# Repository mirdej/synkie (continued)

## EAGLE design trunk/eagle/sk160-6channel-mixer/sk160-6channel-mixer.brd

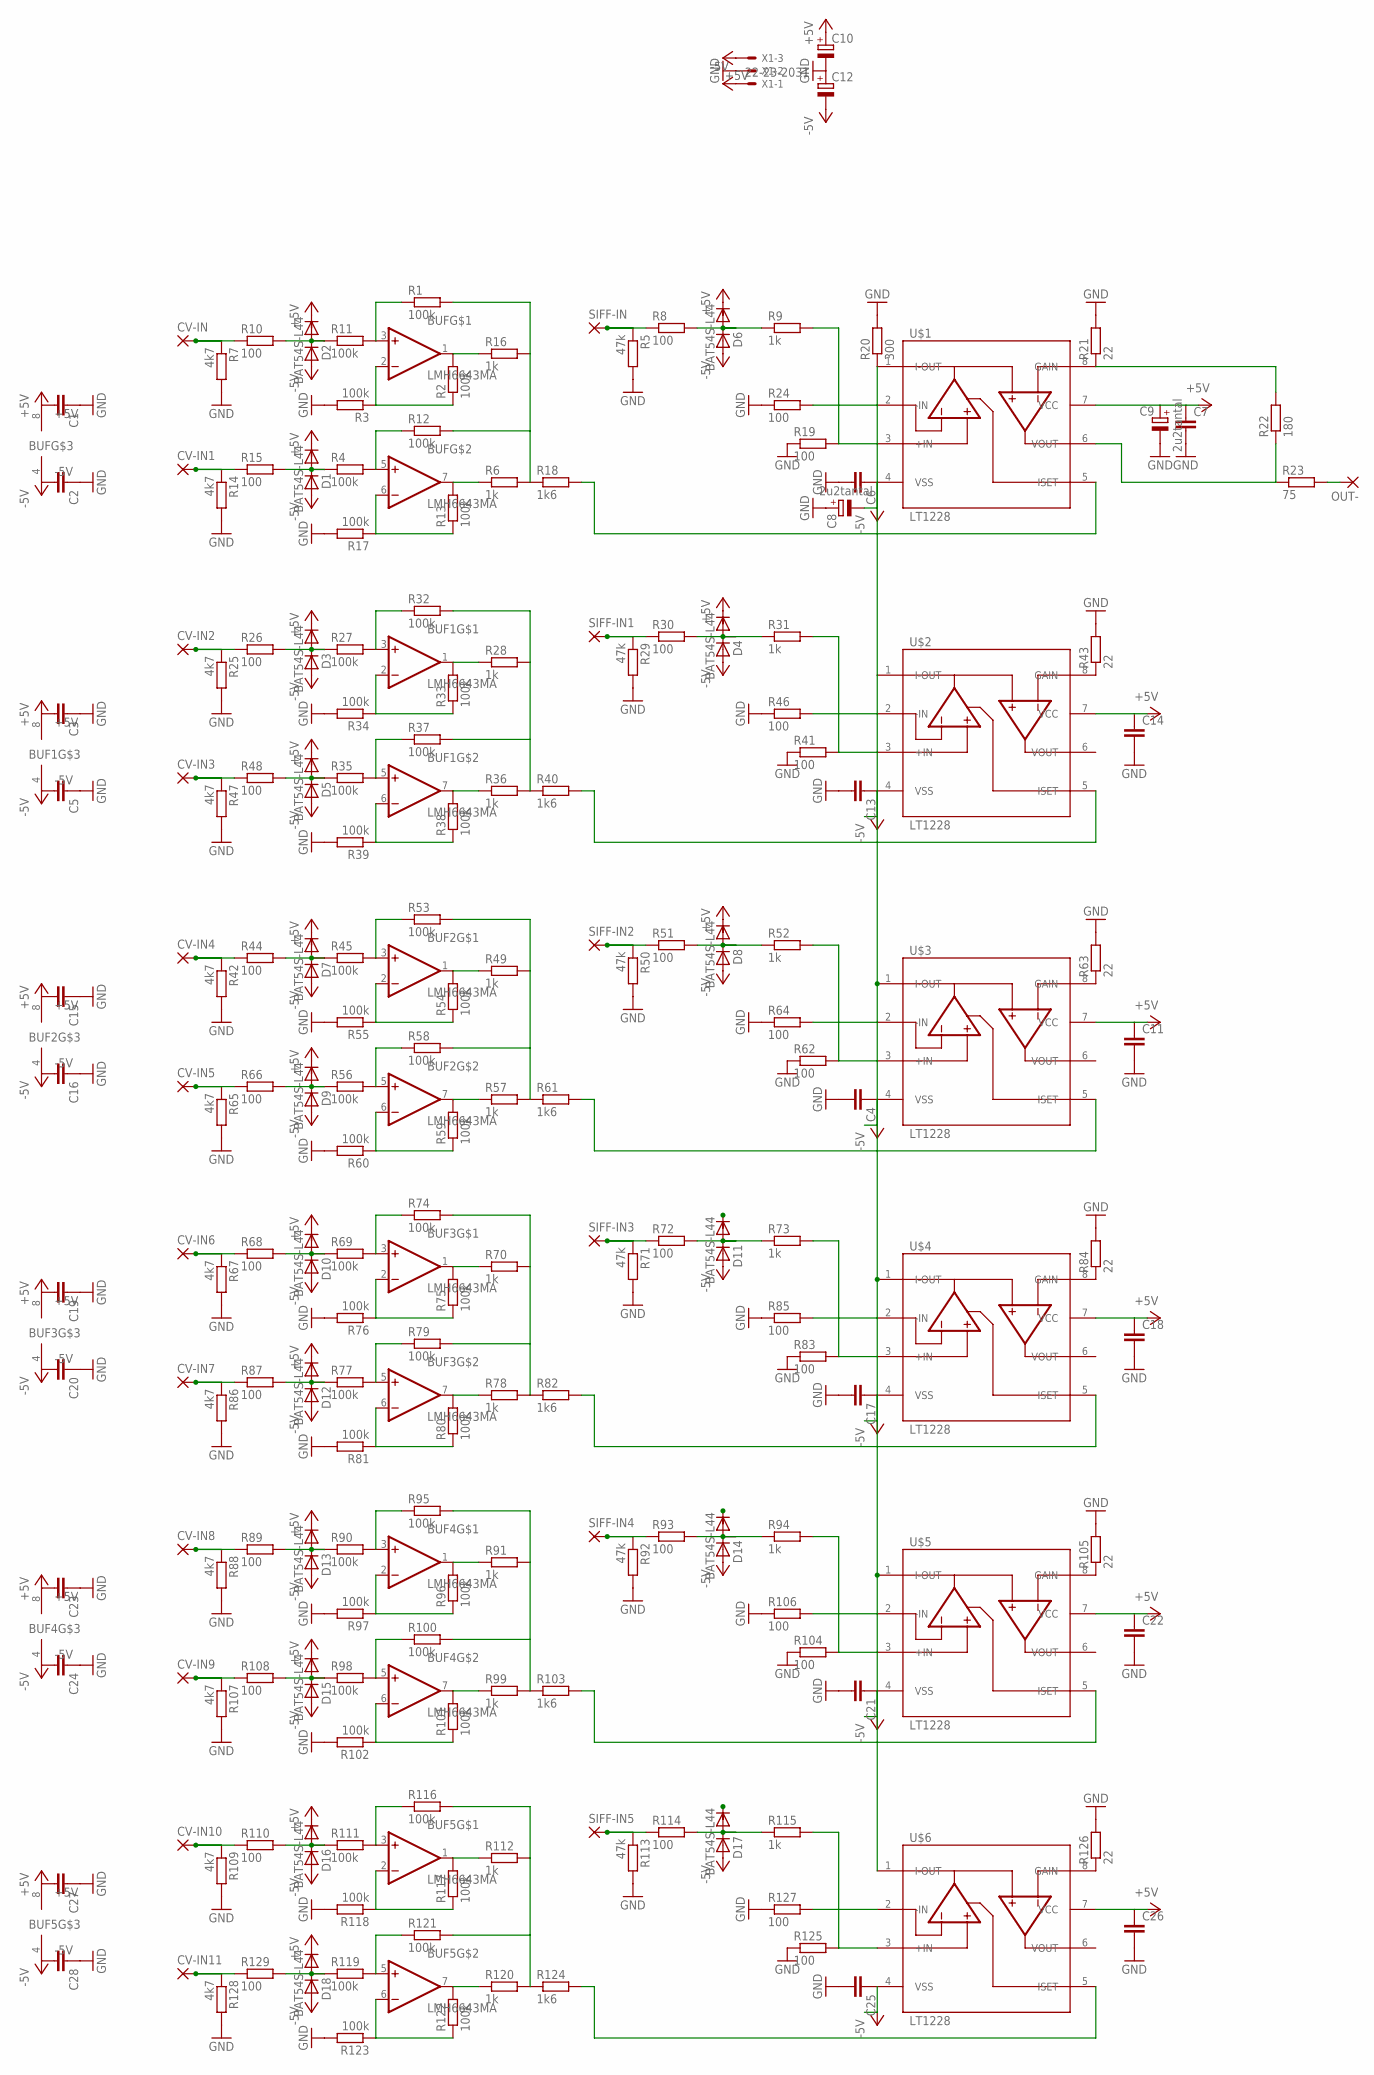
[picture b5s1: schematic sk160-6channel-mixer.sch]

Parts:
BUF, BUF1, BUF2, BUF3, BUF4, BUF5: LMH6643MA; SO08
C1, C2, C3, C4, C5, C6, C7, C11, C13, C14, C15, C16, C17, C18, C19, C20, C21, C22, C23, C24, C25, C26, C27, C28: C-EUC1206; C1206
C8, C9: 2u2tantal; CT6032
C10, C12: CPOL-EUCT6032; CT6032
CV-IN, CV-IN1, CV-IN2, CV-IN3, CV-IN4, CV-IN5, CV-IN6, CV-IN7, CV-IN8, CV-IN9, CV-IN10, CV-IN11: 3,17/1,1
D1, D2, D3, D4, D5, D6, D7, D8, D9, D10, D11, D12, D13, D14, D15, D16, D17, D18: BAT54S-L44; SOT23
OUT-: 3,17/1,1
R1, R2, R3, R4, R11, R12, R13, R17, R27, R32, R33, R34, R35, R37, R38, R39, R45, R53, R54, R55, R56, R58, R59, R60, R69, R74, R75, R76, R77, R79, R80, R81, R90, R95, R96, R97, R98, R100, R101, R102, R111, R116, R117, R118, R119, R121, R122, R123: 100k; R1206
R5, R29, R50, R71, R92, R113: 47k; R1206
R6, R9, R16, R28, R31, R36, R49, R52, R57, R70, R73, R78, R91, R94, R99, R112, R115, R120: 1k; R1206
R7, R14, R25, R42, R47, R65, R67, R86, R88, R107, R109, R128: 4k7; R1206
R8, R10, R15, R19, R24, R26, R30, R41, R44, R46, R48, R51, R62, R64, R66, R68, R72, R83, R85, R87, R89, R93, R104, R106, R108, R110, R114, R125, R127, R129: 100; R1206
R18, R40, R61, R82, R103, R124: 1k6; R1206
R20: 300; R1206
R21, R43, R63, R84, R105, R126: 22; R1206
R22: 180; R1206
R23: 75; R1206
SIFF-IN, SIFF-IN1, SIFF-IN2, SIFF-IN3, SIFF-IN4, SIFF-IN5: 3,17/1,1
U$1, U$2, U$3, U$4, U$5, U$6: LT1228; SO08
X1: 22-23-2031

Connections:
+5V: BUF.8 (+5V), BUF1.8 (+5V), BUF2.8 (+5V), BUF3.8 (+5V), BUF4.8 (+5V), BUF5.8 (+5V), C1.2, C3.2, C7.1, C9.+, C10.+, C11.1, C14.1, C15.2, C18.1, C19.2, C22.1, C23.2, C26.1, C27.2, D1.2 (C), D2.2 (C), D3.2 (C), D4.2 (C), D5.2 (C), D6.2 (C), D7.2 (C), D8.2 (C), D9.2 (C), D10.2 (C), D11.2 (C), D12.2 (C), D13.2 (C), D14.2 (C), D15.2 (C), D16.2 (C), D17.2 (C), D18.2 (C), U$1.7 (VCC), U$2.7 (VCC), U$3.7 (VCC), U$4.7 (VCC), U$5.7 (VCC), U$6.7 (VCC), X1.3
-5V: BUF.4 (-5V), BUF1.4 (-5V), BUF2.4 (-5V), BUF3.4 (-5V), BUF4.4 (-5V), BUF5.4 (-5V), C2.2, C4.1, C5.2, C6.1, C8.-, C12.-, C13.1, C16.2, C17.1, C20.2, C21.1, C24.2, C25.1, C28.2, D1.1 (A), D2.1 (A), D3.1 (A), D4.1 (A), D5.1 (A), D6.1 (A), D7.1 (A), D8.1 (A), D9.1 (A), D10.1 (A), D11.1 (A), D12.1 (A), D13.1 (A), D14.1 (A), D15.1 (A), D16.1 (A), D17.1 (A), D18.1 (A), U$1.4 (VSS), U$2.4 (VSS), U$3.4 (VSS), U$4.4 (VSS), U$5.4 (VSS), U$6.4 (VSS), X1.1
GND: C1.1, C2.1, C3.1, C4.2, C5.1, C6.2, C7.2, C8.+, C9.-, C10.-, C11.2, C12.+, C13.2, C14.2, C15.1, C16.1, C17.2, C18.2, C19.1, C20.1, C21.2, C22.2, C23.1, C24.1, C25.2, C26.2, C27.1, C28.1, R3.2, R5.2, R7.2, R14.2, R17.2, R19.1, R20.2, R21.2, R24.1, R25.2, R29.2, R34.2, R39.2, R41.1, R42.2, R43.2, R46.1, R47.2, R50.2, R55.2, R60.2, R62.1, R63.2, R64.1, R65.2, R67.2, R71.2, R76.2, R81.2, R83.1, R84.2, R85.1, R86.2, R88.2, R92.2, R97.2, R102.2, R104.1, R105.2, R106.1, R107.2, R109.2, R113.2, R118.2, R123.2, R125.1, R126.2, R127.1, R128.2, X1.2
unnamed: CV-IN1.1, R14.1, R15.1
unnamed: D1.3 (AC), R4.1, R15.2
unnamed: CV-IN2.1, R25.1, R26.1
unnamed: BUF.2 (-IN), R2.1, R3.1
unnamed: R9.2, R19.2, U$1.3 (+IN)
unnamed: CV-IN4.1, R42.1, R44.1
unnamed: BUF.5 (+IN), R4.2, R12.1
unnamed: BUF.7 (OUT), R6.1, R13.2
unnamed: R21.1, R22.2, U$1.8 (GAIN)
unnamed: CV-IN.1, R7.1, R10.1
unnamed: D2.3 (AC), R10.2, R11.1
unnamed: BUF.6 (-IN), R13.1, R17.1
unnamed: D3.3 (AC), R26.2, R27.1
unnamed: BUF.3 (+IN), R1.1, R11.2
unnamed: R5.1, R8.1, SIFF-IN.1
unnamed: D6.3 (AC), R8.2, R9.1
unnamed: BUF.1 (OUT), R2.2, R16.1
unnamed: R18.2, U$1.5 (ISET)
unnamed: R1.2, R6.2, R12.2, R16.2, R18.1
unnamed: R22.1, R23.1, U$1.6 (VOUT)
unnamed: OUT-.1, R23.2
unnamed: R24.2, U$1.2 (-IN)
unnamed: BUF1.3 (+IN), R27.2, R32.1
unnamed: BUF1.1 (OUT), R28.1, R33.2
unnamed: R28.2, R32.2, R36.2, R37.2, R40.1
unnamed: R29.1, R30.1, SIFF-IN1.1
unnamed: D4.3 (AC), R30.2, R31.1
unnamed: R31.2, R41.2, U$2.3 (+IN)
unnamed: BUF1.2 (-IN), R33.1, R34.1
unnamed: BUF1.5 (+IN), R35.2, R37.1
unnamed: BUF1.7 (OUT), R36.1, R38.2
unnamed: BUF1.6 (-IN), R38.1, R39.1
unnamed: R40.2, U$2.5 (ISET)
unnamed: R20.1, U$1.1 (I-OUT), U$2.1 (I-OUT), U$3.1 (I-OUT), U$4.1 (I-OUT), U$5.1 (I-OUT), U$6.1 (I-OUT)
unnamed: D7.3 (AC), R44.2, R45.1
unnamed: BUF2.3 (+IN), R45.2, R53.1
unnamed: BUF2.1 (OUT), R49.1, R54.2
unnamed: R46.2, U$2.2 (-IN)
unnamed: CV-IN3.1, R47.1, R48.1
unnamed: D5.3 (AC), R35.1, R48.2
unnamed: R49.2, R53.2, R57.2, R58.2, R61.1
unnamed: R43.1, U$2.8 (GAIN)
unnamed: R50.1, R51.1, SIFF-IN2.1
unnamed: D8.3 (AC), R51.2, R52.1
unnamed: R52.2, R62.2, U$3.3 (+IN)
unnamed: BUF2.2 (-IN), R54.1, R55.1
unnamed: BUF2.5 (+IN), R56.2, R58.1
unnamed: BUF2.7 (OUT), R57.1, R59.2
unnamed: BUF2.6 (-IN), R59.1, R60.1
unnamed: R61.2, U$3.5 (ISET)
unnamed: R64.2, U$3.2 (-IN)
unnamed: CV-IN5.1, R65.1, R66.1
unnamed: D9.3 (AC), R56.1, R66.2
unnamed: R63.1, U$3.8 (GAIN)
unnamed: CV-IN6.1, R67.1, R68.1
unnamed: D10.3 (AC), R68.2, R69.1
unnamed: BUF3.3 (+IN), R69.2, R74.1
unnamed: BUF3.1 (OUT), R70.1, R75.2
unnamed: R70.2, R74.2, R78.2, R79.2, R82.1
unnamed: R71.1, R72.1, SIFF-IN3.1
unnamed: D11.3 (AC), R72.2, R73.1
unnamed: R73.2, R83.2, U$4.3 (+IN)
unnamed: BUF3.2 (-IN), R75.1, R76.1
unnamed: BUF3.5 (+IN), R77.2, R79.1
unnamed: BUF3.7 (OUT), R78.1, R80.2
unnamed: BUF3.6 (-IN), R80.1, R81.1
unnamed: R82.2, U$4.5 (ISET)
unnamed: R85.2, U$4.2 (-IN)
unnamed: CV-IN7.1, R86.1, R87.1
unnamed: D12.3 (AC), R77.1, R87.2
unnamed: R84.1, U$4.8 (GAIN)
unnamed: CV-IN8.1, R88.1, R89.1
unnamed: D13.3 (AC), R89.2, R90.1
unnamed: BUF4.3 (+IN), R90.2, R95.1
unnamed: BUF4.1 (OUT), R91.1, R96.2
unnamed: R91.2, R95.2, R99.2, R100.2, R103.1
unnamed: R92.1, R93.1, SIFF-IN4.1
unnamed: D14.3 (AC), R93.2, R94.1
unnamed: R94.2, R104.2, U$5.3 (+IN)
unnamed: BUF4.2 (-IN), R96.1, R97.1
unnamed: BUF4.5 (+IN), R98.2, R100.1
unnamed: BUF4.7 (OUT), R99.1, R101.2
unnamed: BUF4.6 (-IN), R101.1, R102.1
unnamed: R103.2, U$5.5 (ISET)
unnamed: R106.2, U$5.2 (-IN)
unnamed: CV-IN9.1, R107.1, R108.1
unnamed: D15.3 (AC), R98.1, R108.2
unnamed: R105.1, U$5.8 (GAIN)
unnamed: CV-IN10.1, R109.1, R110.1
unnamed: D16.3 (AC), R110.2, R111.1
unnamed: BUF5.3 (+IN), R111.2, R116.1
unnamed: BUF5.1 (OUT), R112.1, R117.2
unnamed: R112.2, R116.2, R120.2, R121.2, R124.1
unnamed: R113.1, R114.1, SIFF-IN5.1
unnamed: D17.3 (AC), R114.2, R115.1
unnamed: R115.2, R125.2, U$6.3 (+IN)
unnamed: BUF5.2 (-IN), R117.1, R118.1
unnamed: BUF5.5 (+IN), R119.2, R121.1
unnamed: BUF5.7 (OUT), R120.1, R122.2
unnamed: BUF5.6 (-IN), R122.1, R123.1
unnamed: R124.2, U$6.5 (ISET)
unnamed: R127.2, U$6.2 (-IN)
unnamed: CV-IN11.1, R128.1, R129.1
unnamed: D18.3 (AC), R119.1, R129.2
unnamed: R126.1, U$6.8 (GAIN)

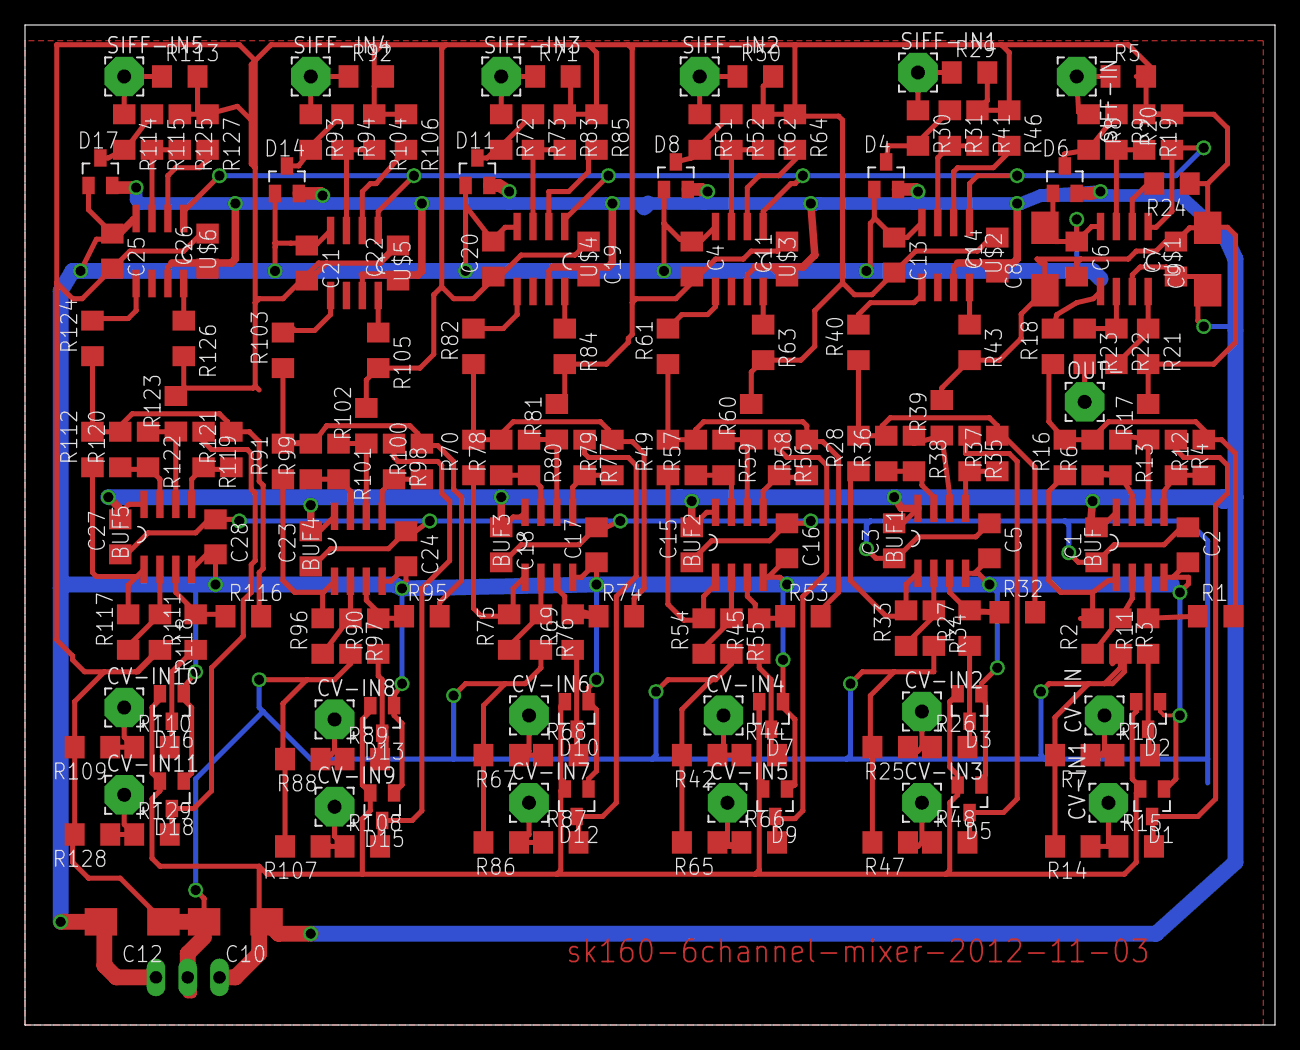
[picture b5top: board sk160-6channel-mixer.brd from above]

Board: 2 copper layers, 100.0 x 80.0 mm, 207 parts (1 on the bottom side), 108 nets.
